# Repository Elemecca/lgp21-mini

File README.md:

# LGP-21 Mini

The LGP-21 is an early transistorized computer manufactured by
the Librascope division of General Precision starting in 1963.
If you want to see the original computer in action, Usagi Electric
created [a series of excellent videos][usagi].

This project is a miniature replica of the LGP-21. It aims to be
as close to electrically identical to the original as possible
without relying on out-of-production components like germanium
transistors.

[usagi]: https://www.youtube.com/playlist?list=PLnw98JPyObn17qO83Hy1PHKtXimH4rYbU

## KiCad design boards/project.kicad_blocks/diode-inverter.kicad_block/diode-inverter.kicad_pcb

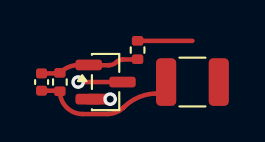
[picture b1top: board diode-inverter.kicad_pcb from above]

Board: 2 copper layers, 5 parts (0 on the bottom side), 2 nets.

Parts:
C17: 120p; C_0402_1005Metric
Q64: MMBT5401; SOT-23
R316: 6k8; R_0402_1005Metric
R355: 10k ½W; R_1210_3225Metric
R356: 33k; R_0402_1005Metric

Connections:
unnamed: C17.2, R316.1, R355.2
unnamed: C17.1, Q64.1 (B), R316.2, R356.1

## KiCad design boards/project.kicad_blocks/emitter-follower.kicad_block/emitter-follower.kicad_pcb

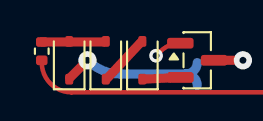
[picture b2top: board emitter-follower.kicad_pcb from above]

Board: 2 copper layers, 5 parts (0 on the bottom side), 3 nets.

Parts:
CR11, CR12, CR13: 1N4148WS; D_SOD-323
Q26: MMBT5401; SOT-23
R200: 56k; R_0402_1005Metric

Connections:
unnamed: CR12.1 (K), CR13.2 (A)
unnamed: CR13.1 (K), Q26.2 (E)
~G: CR11.2 (A), CR12.2 (A), R200.1

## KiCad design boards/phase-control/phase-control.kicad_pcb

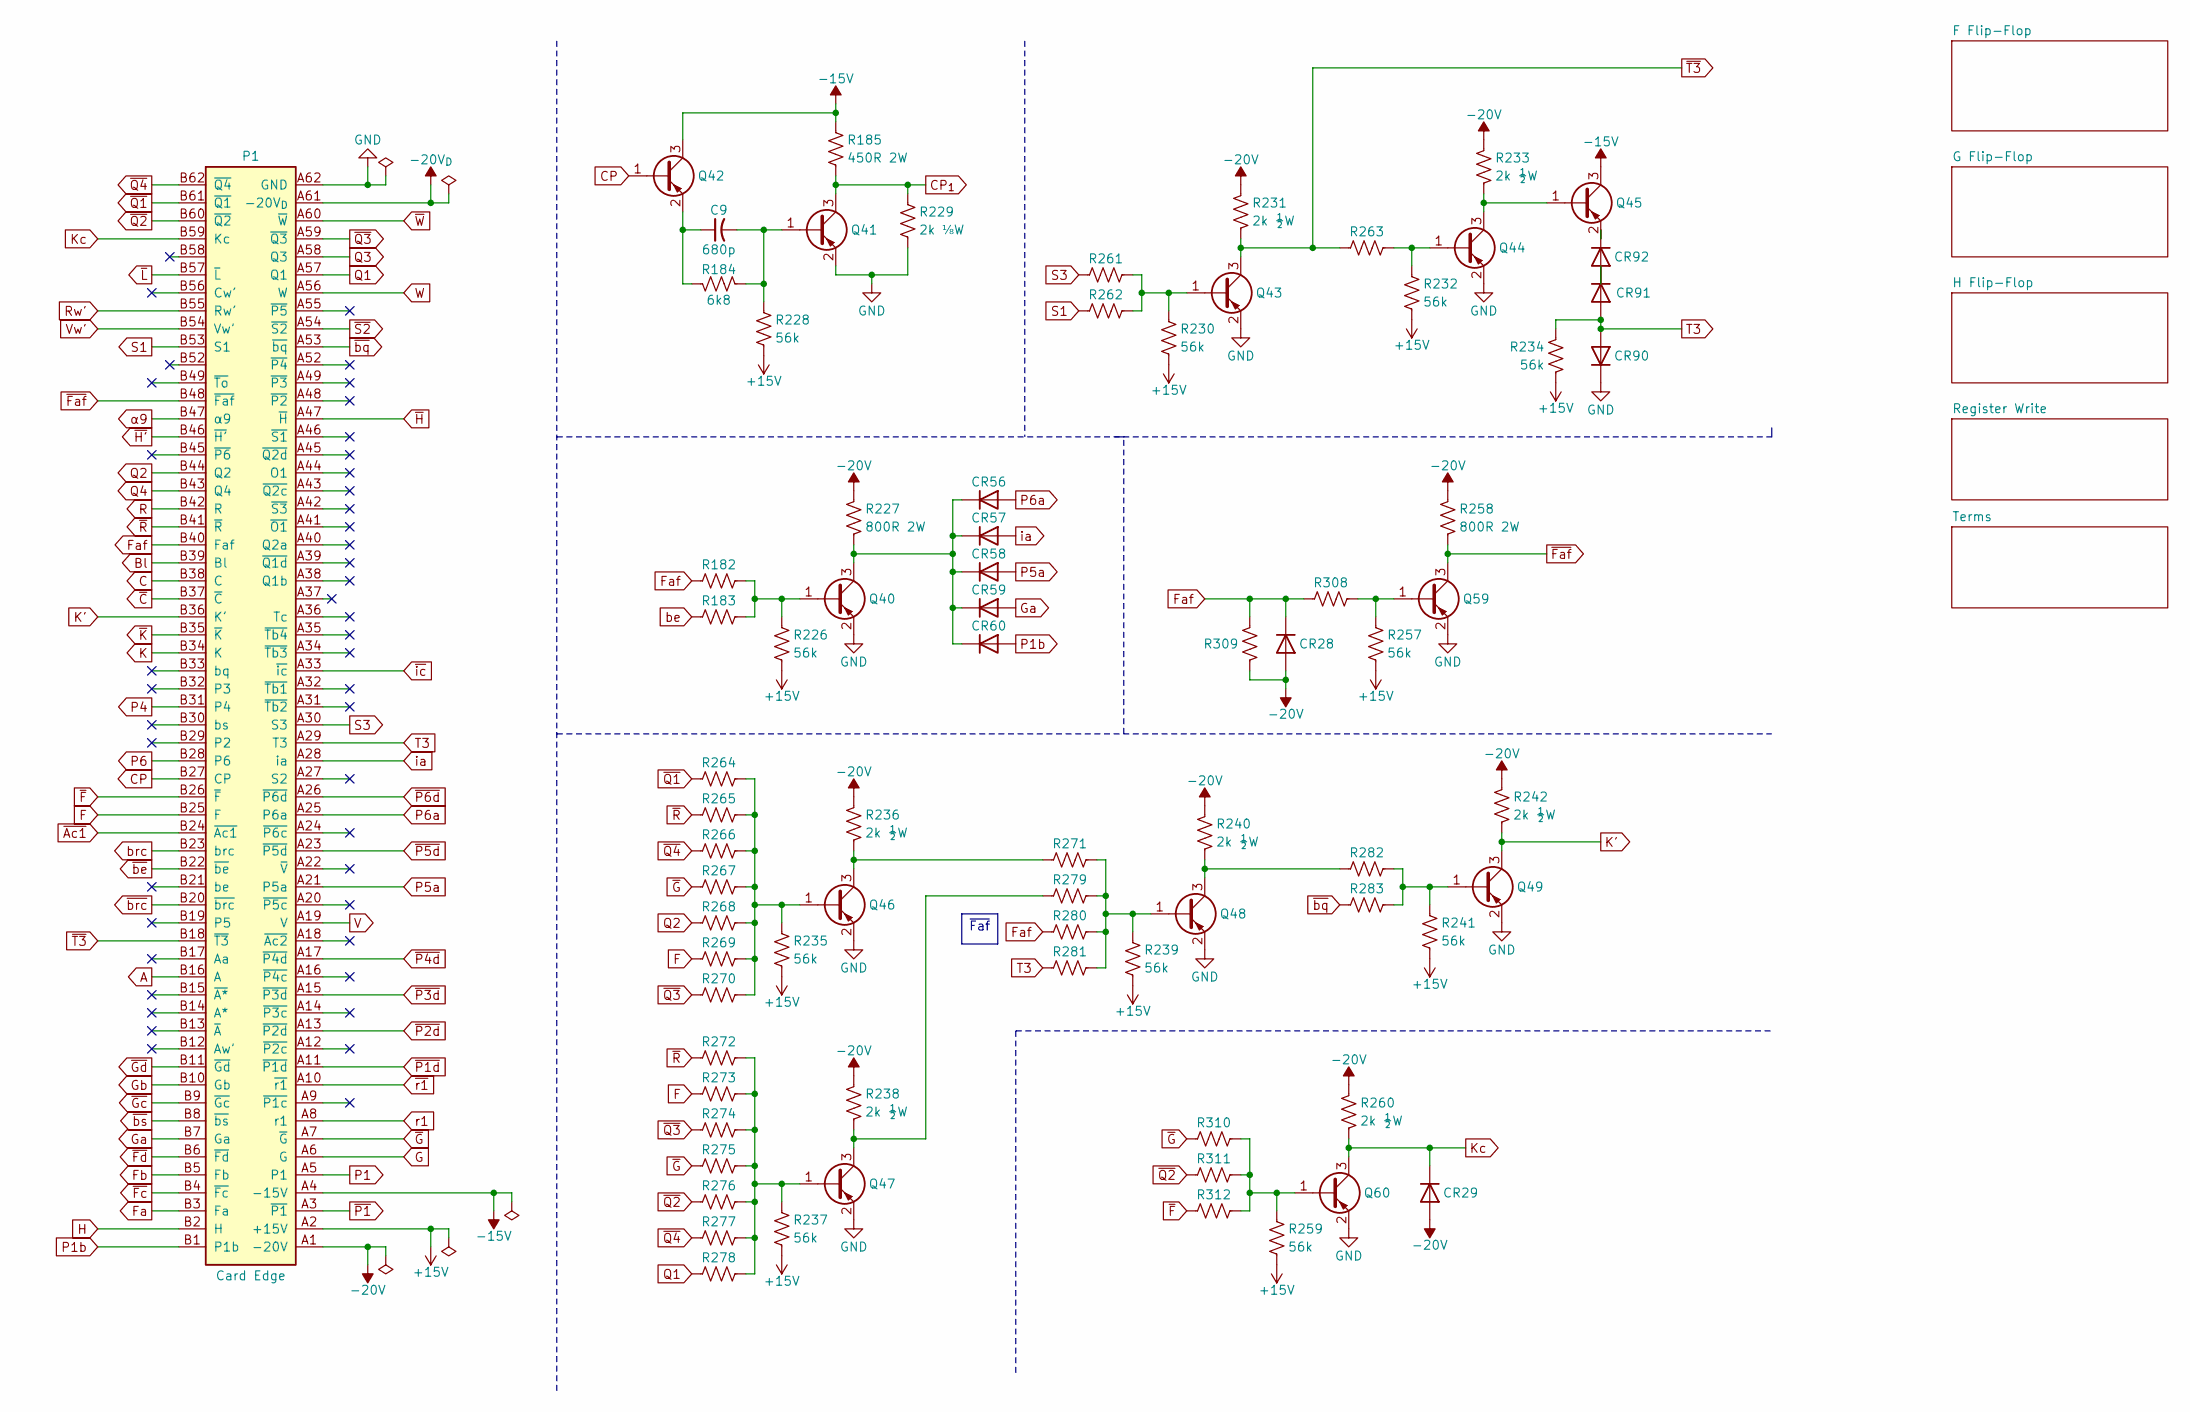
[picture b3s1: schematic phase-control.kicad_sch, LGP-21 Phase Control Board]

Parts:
C9: 680p; C_0402_1005Metric
CR28, CR29, CR56, CR57, CR58, CR59, CR60, CR90, CR91, CR92: 1N4148WS; D_SOD-323; LCSC C2128
P1: Card Edge; Bus_PCI_5V_32bit
Q40, Q41, Q42, Q43, Q44, Q45, Q46, Q47, Q48, Q49, Q59, Q60: MMBT5401; SOT-23; LCSC C8326
R182, R183, R261, R262, R263, R264, R265, R266, R267, R268, R269, R270, R271, R272, R273, R274, R275, R276, R277, R278, R279, R280, R281, R282, R283, R308, R309, R310, R311, R312: 15k; R_0402_1005Metric
R184: 6k8; R_0402_1005Metric
R185: 450R 2W; R_Axial_DIN0516_L15.5mm_D5.0mm_P20.32mm_Horizontal
R226, R228, R230, R232, R234, R235, R237, R239, R241, R257, R259: 56k; R_0402_1005Metric
R227, R258: 800R 2W; R_Axial_DIN0516_L15.5mm_D5.0mm_P20.32mm_Horizontal
R229: 2k ⅛W; R_0805_2012Metric
R231, R233, R236, R238, R240, R242, R260: 2k ½W; R_1210_3225Metric

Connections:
+15V: P1.A2 (+15V), R226.2, R228.2, R230.2, R232.2, R234.2, R235.2, R237.2, R239.2, R241.2, R257.2, R259.2; also elsewhere on the board
-15V: P1.A4 (-15V), Q42.3 (C), Q45.3 (C), R185.1; also elsewhere on the board
-20V: CR28.2 (A), CR29.2 (A), P1.A1 (-20V), R227.1, R231.1, R233.1, R236.1, R238.1, R240.1, R242.1, R258.1, R260.1, R309.2; also elsewhere on the board
-20V_{D}: P1.A61 (-20V_{D}); also elsewhere on the board
A: P1.B16 (A); also elsewhere on the board
Bl: P1.B39 (Bl); also elsewhere on the board
C: P1.B38 (C); also elsewhere on the board
CP: P1.B27 (CP), Q42.1 (B); also elsewhere on the board
CP_{1}: Q41.3 (C), R185.2, R229.1; also elsewhere on the board
F: P1.B25 (F), R269.1, R273.1; also elsewhere on the board
Fa: P1.B3 (Fa); also elsewhere on the board
Faf: CR28.1 (K), P1.B40 (Faf), R182.1, R280.1, R308.1, R309.1
Fb: P1.B5 (Fb); also elsewhere on the board
G: P1.A6 (G); also elsewhere on the board
GND: CR90.1 (K), P1.A62 (GND), Q40.2 (E), Q41.2 (E), Q43.2 (E), Q44.2 (E), Q46.2 (E), Q47.2 (E), Q48.2 (E), Q49.2 (E), Q59.2 (E), Q60.2 (E), R229.2; also elsewhere on the board
Ga: CR59.2 (A), P1.B7 (Ga); also elsewhere on the board
Gb: P1.B10 (Gb); also elsewhere on the board
H: P1.B2 (H); also elsewhere on the board
K: P1.B34 (K); also elsewhere on the board
K': P1.B36 (K'), Q49.3 (C), R242.2
Kc: CR29.1 (K), P1.B59 (Kc), Q60.3 (C), R260.2
unnamed: CR56.1 (K), CR57.1 (K), CR58.1 (K), CR59.1 (K), CR60.1 (K), Q40.3 (C), R227.2
unnamed: CR91.1 (K), CR92.2 (A)
unnamed: CR92.1 (K), Q45.2 (E)
unnamed: Q40.1 (B), R182.2, R183.2, R226.1
unnamed: C9.2, Q41.1 (B), R184.2, R228.1
unnamed: C9.1, Q42.2 (E), R184.1
unnamed: Q43.1 (B), R230.1, R261.2, R262.2
unnamed: Q44.1 (B), R232.1, R263.2
unnamed: Q44.3 (C), Q45.1 (B), R233.2
unnamed: Q46.1 (B), R235.1, R264.2, R265.2, R266.2, R267.2, R268.2, R269.2, R270.2
unnamed: Q46.3 (C), R236.2, R271.1
unnamed: Q47.1 (B), R237.1, R272.2, R273.2, R274.2, R275.2, R276.2, R277.2, R278.2
unnamed: Q47.3 (C), R238.2, R279.1
unnamed: Q48.1 (B), R239.1, R271.2, R279.2, R280.2, R281.2
unnamed: Q48.3 (C), R240.2, R282.1
unnamed: Q49.1 (B), R241.1, R282.2, R283.2
unnamed: Q59.1 (B), R257.1, R308.2
unnamed: Q60.1 (B), R259.1, R310.2, R311.2, R312.2
P1: P1.A5 (P1); also elsewhere on the board
P1b: CR60.2 (A), P1.B1 (P1b)
P4: P1.B31 (P4); also elsewhere on the board
P5a: CR58.2 (A), P1.A21 (P5a)
P6: P1.B28 (P6); also elsewhere on the board
P6a: CR56.2 (A), P1.A25 (P6a)
Q1: P1.A57 (Q1), R278.1; also elsewhere on the board
Q2: P1.B44 (Q2), R268.1; also elsewhere on the board
Q3: P1.A58 (Q3); also elsewhere on the board
Q4: P1.B43 (Q4); also elsewhere on the board
R: P1.B42 (R); also elsewhere on the board
Rw': P1.B55 (Rw'); also elsewhere on the board
S1: P1.B53 (S1), R262.1
S3: P1.A30 (S3), R261.1
T3: CR90.2 (A), CR91.2 (A), P1.A29 (T3), R234.1, R281.1; also elsewhere on the board
V: P1.A19 (V); also elsewhere on the board
Vw': P1.B54 (Vw'); also elsewhere on the board
W: P1.A56 (W); also elsewhere on the board
be: R183.1; also elsewhere on the board
brc: P1.B23 (brc); also elsewhere on the board
ia: CR57.2 (A), P1.A28 (ia)
r1: P1.A8 (r1); also elsewhere on the board
~Ac1: P1.B24 (~Ac1); also elsewhere on the board
~C: P1.B37 (~C); also elsewhere on the board
~Faf: P1.B48 (~Faf), Q59.3 (C), R258.2; also elsewhere on the board
~Fc: P1.B4 (~Fc); also elsewhere on the board
~Fd: P1.B6 (~Fd); also elsewhere on the board
~F: P1.B26 (~F), R312.1; also elsewhere on the board
~Gc: P1.B9 (~Gc); also elsewhere on the board
~Gd: P1.B11 (~Gd); also elsewhere on the board
~G: P1.A7 (~G), R267.1, R275.1, R310.1; also elsewhere on the board
~H': P1.B46 (~H'); also elsewhere on the board
~H: P1.A47 (~H); also elsewhere on the board
~K: P1.B35 (~K); also elsewhere on the board
~L: P1.B57 (~L); also elsewhere on the board
~P1d: P1.A11 (~P1d); also elsewhere on the board
~P1: P1.A3 (~P1); also elsewhere on the board
~P2d: P1.A13 (~P2d); also elsewhere on the board
~P3d: P1.A15 (~P3d); also elsewhere on the board
~P4d: P1.A17 (~P4d); also elsewhere on the board
~P5d: P1.A23 (~P5d); also elsewhere on the board
~P6d: P1.A26 (~P6d); also elsewhere on the board
~Q1: P1.B61 (~Q1), R264.1; also elsewhere on the board
~Q2: P1.B60 (~Q2), R276.1, R311.1; also elsewhere on the board
~Q3: P1.A59 (~Q3), R270.1, R274.1; also elsewhere on the board
~Q4: P1.B62 (~Q4), R266.1, R277.1; also elsewhere on the board
~R: P1.B41 (~R), R265.1, R272.1
~S2: P1.A54 (~S2); also elsewhere on the board
~T3: P1.B18 (~T3), Q43.3 (C), R231.2, R263.1
~W: P1.A60 (~W); also elsewhere on the board
~be: P1.B22 (~be); also elsewhere on the board
~bq: P1.A53 (~bq), R283.1
~brc: P1.B20 (~brc); also elsewhere on the board
~bs: P1.B8 (~bs); also elsewhere on the board
~ic: P1.A33 (~ic); also elsewhere on the board
~r1: P1.A10 (~r1); also elsewhere on the board
α9: P1.B47 (α9); also elsewhere on the board

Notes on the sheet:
~{Faf}

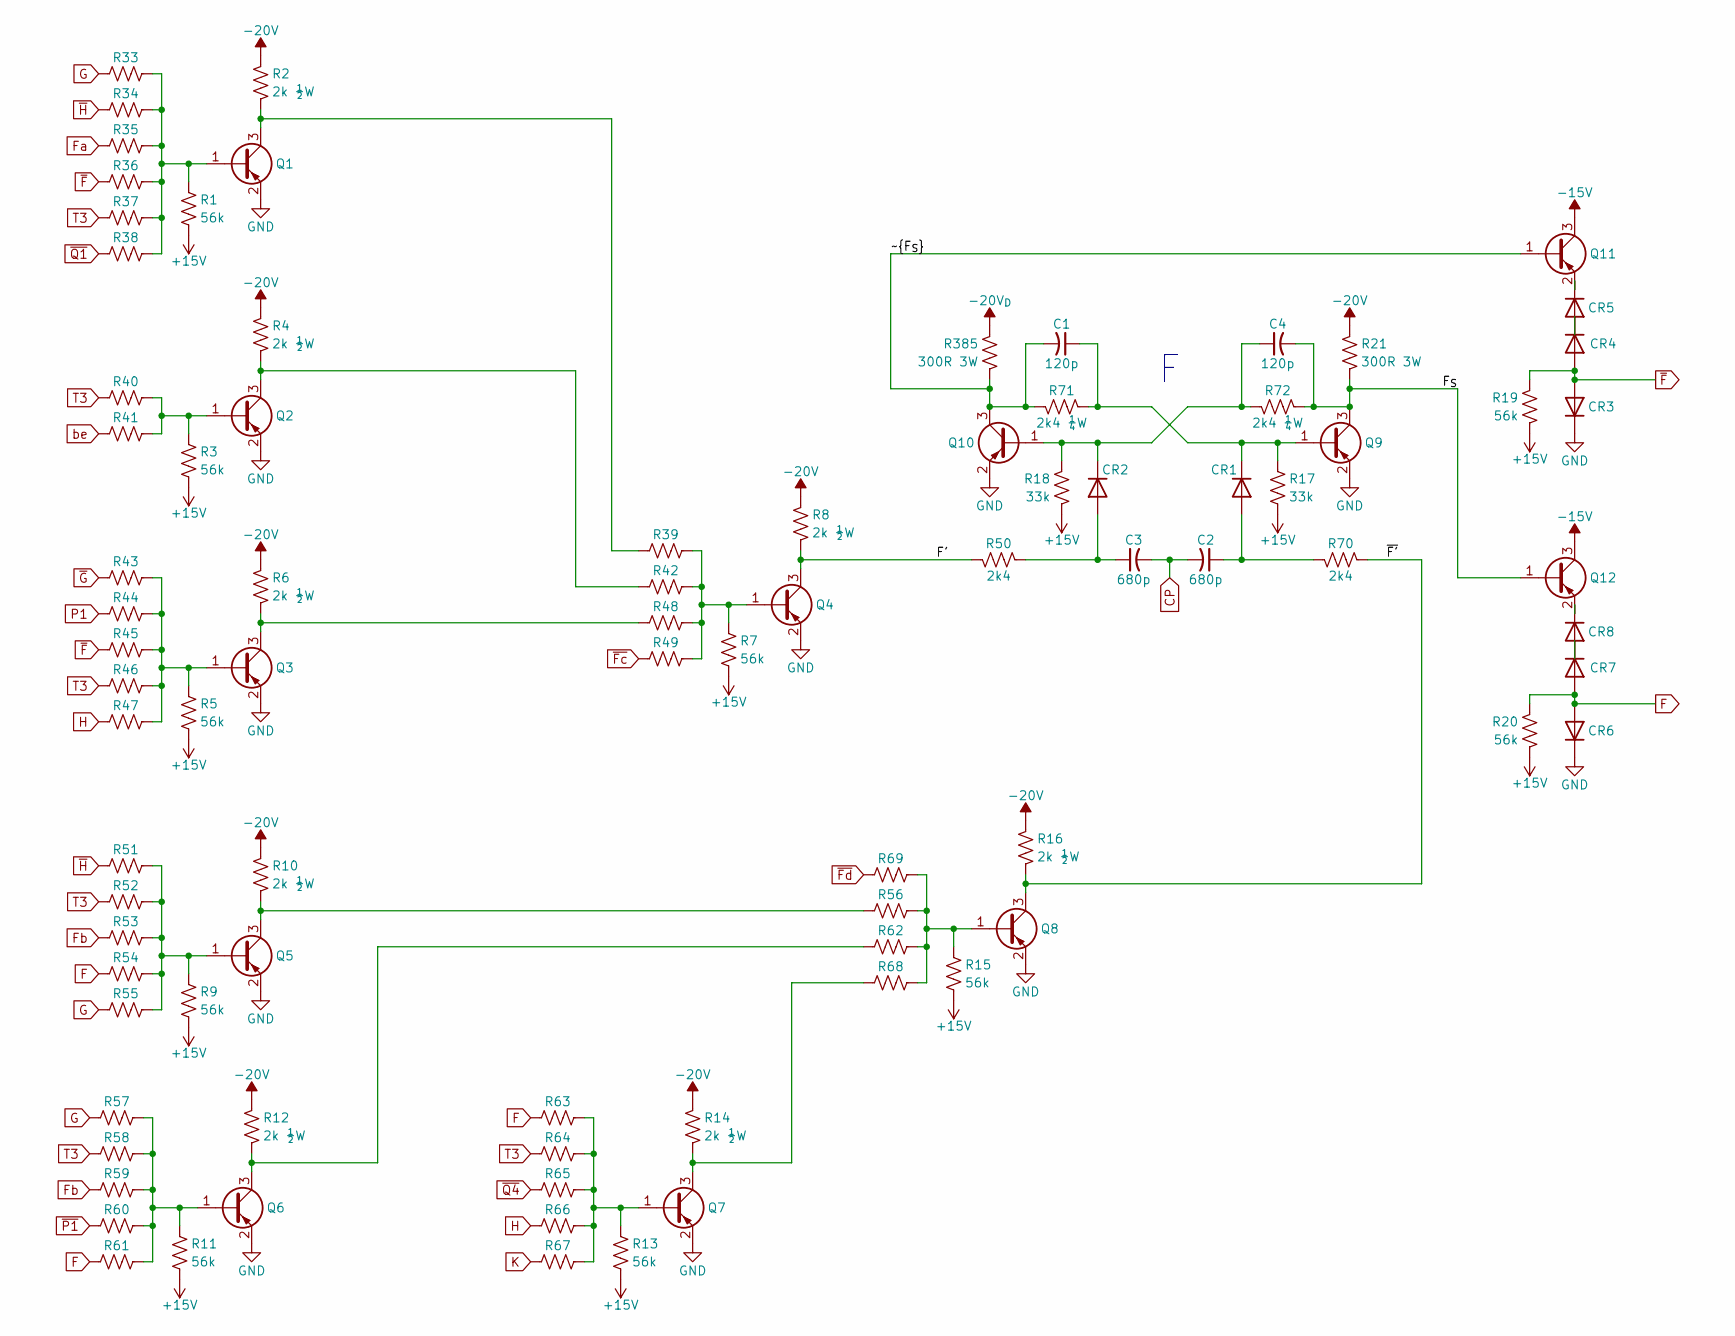
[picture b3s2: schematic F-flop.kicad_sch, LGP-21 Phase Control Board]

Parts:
C1, C4: 120p; C_0402_1005Metric
C2, C3: 680p; C_0402_1005Metric
CR1, CR2, CR3, CR4, CR5, CR6, CR7, CR8: 1N4148WS; D_SOD-323; LCSC C2128
Q1, Q2, Q3, Q4, Q5, Q6, Q7, Q8, Q9, Q10, Q11, Q12: MMBT5401; SOT-23; LCSC C8326
R1, R3, R5, R7, R9, R11, R13, R15, R19, R20: 56k; R_0402_1005Metric
R2, R4, R6, R8, R10, R12, R14, R16: 2k ½W; R_1210_3225Metric
R17, R18: 33k; R_0402_1005Metric
R21, R385: 300R 3W; R_Axial_DIN0516_L15.5mm_D5.0mm_P20.32mm_Horizontal
R33, R34, R35, R36, R37, R38, R39, R40, R41, R42, R43, R44, R45, R46, R47, R48, R49, R51, R52, R53, R54, R55, R56, R57, R58, R59, R60, R61, R62, R63, R64, R65, R66, R67, R68, R69: 15k; R_0402_1005Metric
R50, R70: 2k4; R_0402_1005Metric
R71, R72: 2k4 ¼W; R_0603_1608Metric

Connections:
+15V: R1.2, R3.2, R5.2, R7.2, R9.2, R11.2, R13.2, R15.2, R17.2, R18.2, R19.2, R20.2; also elsewhere on the board
-15V: Q11.3 (C), Q12.3 (C); also elsewhere on the board
-20V: R2.1, R4.1, R6.1, R8.1, R10.1, R12.1, R14.1, R16.1, R21.1; also elsewhere on the board
-20V_{D}: R385.1; also elsewhere on the board
/F Flip-Flop/F': Q4.3 (C), R8.2, R50.1
/F Flip-Flop/F_{S}: C4.2, Q9.3 (C), Q12.1 (B), R21.2, R72.2
/F Flip-Flop/~F': Q8.3 (C), R16.2, R70.2
/F Flip-Flop/~F_{S}: C1.2, Q10.3 (C), Q11.1 (B), R71.1, R385.2
CP: C2.2, C3.2; also elsewhere on the board
F: CR6.2 (A), CR7.2 (A), R20.1, R54.1, R61.1, R63.1; also elsewhere on the board
Fa: R35.1; also elsewhere on the board
Fb: R53.1, R59.1; also elsewhere on the board
G: R33.1, R55.1, R57.1; also elsewhere on the board
GND: CR3.1 (K), CR6.1 (K), Q1.2 (E), Q2.2 (E), Q3.2 (E), Q4.2 (E), Q5.2 (E), Q6.2 (E), Q7.2 (E), Q8.2 (E), Q9.2 (E), Q10.2 (E); also elsewhere on the board
H: R47.1, R66.1; also elsewhere on the board
K: R67.1; also elsewhere on the board
unnamed: C2.1, CR1.2 (A), R70.1
unnamed: C1.1, CR1.1 (K), Q9.1 (B), R17.1, R71.2
unnamed: C3.1, CR2.2 (A), R50.2
unnamed: C4.1, CR2.1 (K), Q10.1 (B), R18.1, R72.1
unnamed: CR4.1 (K), CR5.2 (A)
unnamed: CR5.1 (K), Q11.2 (E)
unnamed: CR7.1 (K), CR8.2 (A)
unnamed: CR8.1 (K), Q12.2 (E)
unnamed: Q1.1 (B), R1.1, R33.2, R34.2, R35.2, R36.2, R37.2, R38.2
unnamed: Q1.3 (C), R2.2, R39.1
unnamed: Q2.1 (B), R3.1, R40.2, R41.2
unnamed: Q2.3 (C), R4.2, R42.1
unnamed: Q3.1 (B), R5.1, R43.2, R44.2, R45.2, R46.2, R47.2
unnamed: Q3.3 (C), R6.2, R48.1
unnamed: Q4.1 (B), R7.1, R39.2, R42.2, R48.2, R49.2
unnamed: Q5.1 (B), R9.1, R51.2, R52.2, R53.2, R54.2, R55.2
unnamed: Q5.3 (C), R10.2, R56.1
unnamed: Q6.1 (B), R11.1, R57.2, R58.2, R59.2, R60.2, R61.2
unnamed: Q6.3 (C), R12.2, R62.1
unnamed: Q7.1 (B), R13.1, R63.2, R64.2, R65.2, R66.2, R67.2
unnamed: Q7.3 (C), R14.2, R68.1
unnamed: Q8.1 (B), R15.1, R56.2, R62.2, R68.2, R69.2
P1: R44.1; also elsewhere on the board
T3: R37.1, R40.1, R46.1, R52.1, R58.1, R64.1; also elsewhere on the board
be: R41.1; also elsewhere on the board
~Fc: R49.1; also elsewhere on the board
~Fd: R69.1; also elsewhere on the board
~F: CR3.2 (A), CR4.2 (A), R19.1, R36.1, R45.1; also elsewhere on the board
~G: R43.1; also elsewhere on the board
~H: R34.1, R51.1; also elsewhere on the board
~P1: R60.1; also elsewhere on the board
~Q1: R38.1; also elsewhere on the board
~Q4: R65.1; also elsewhere on the board

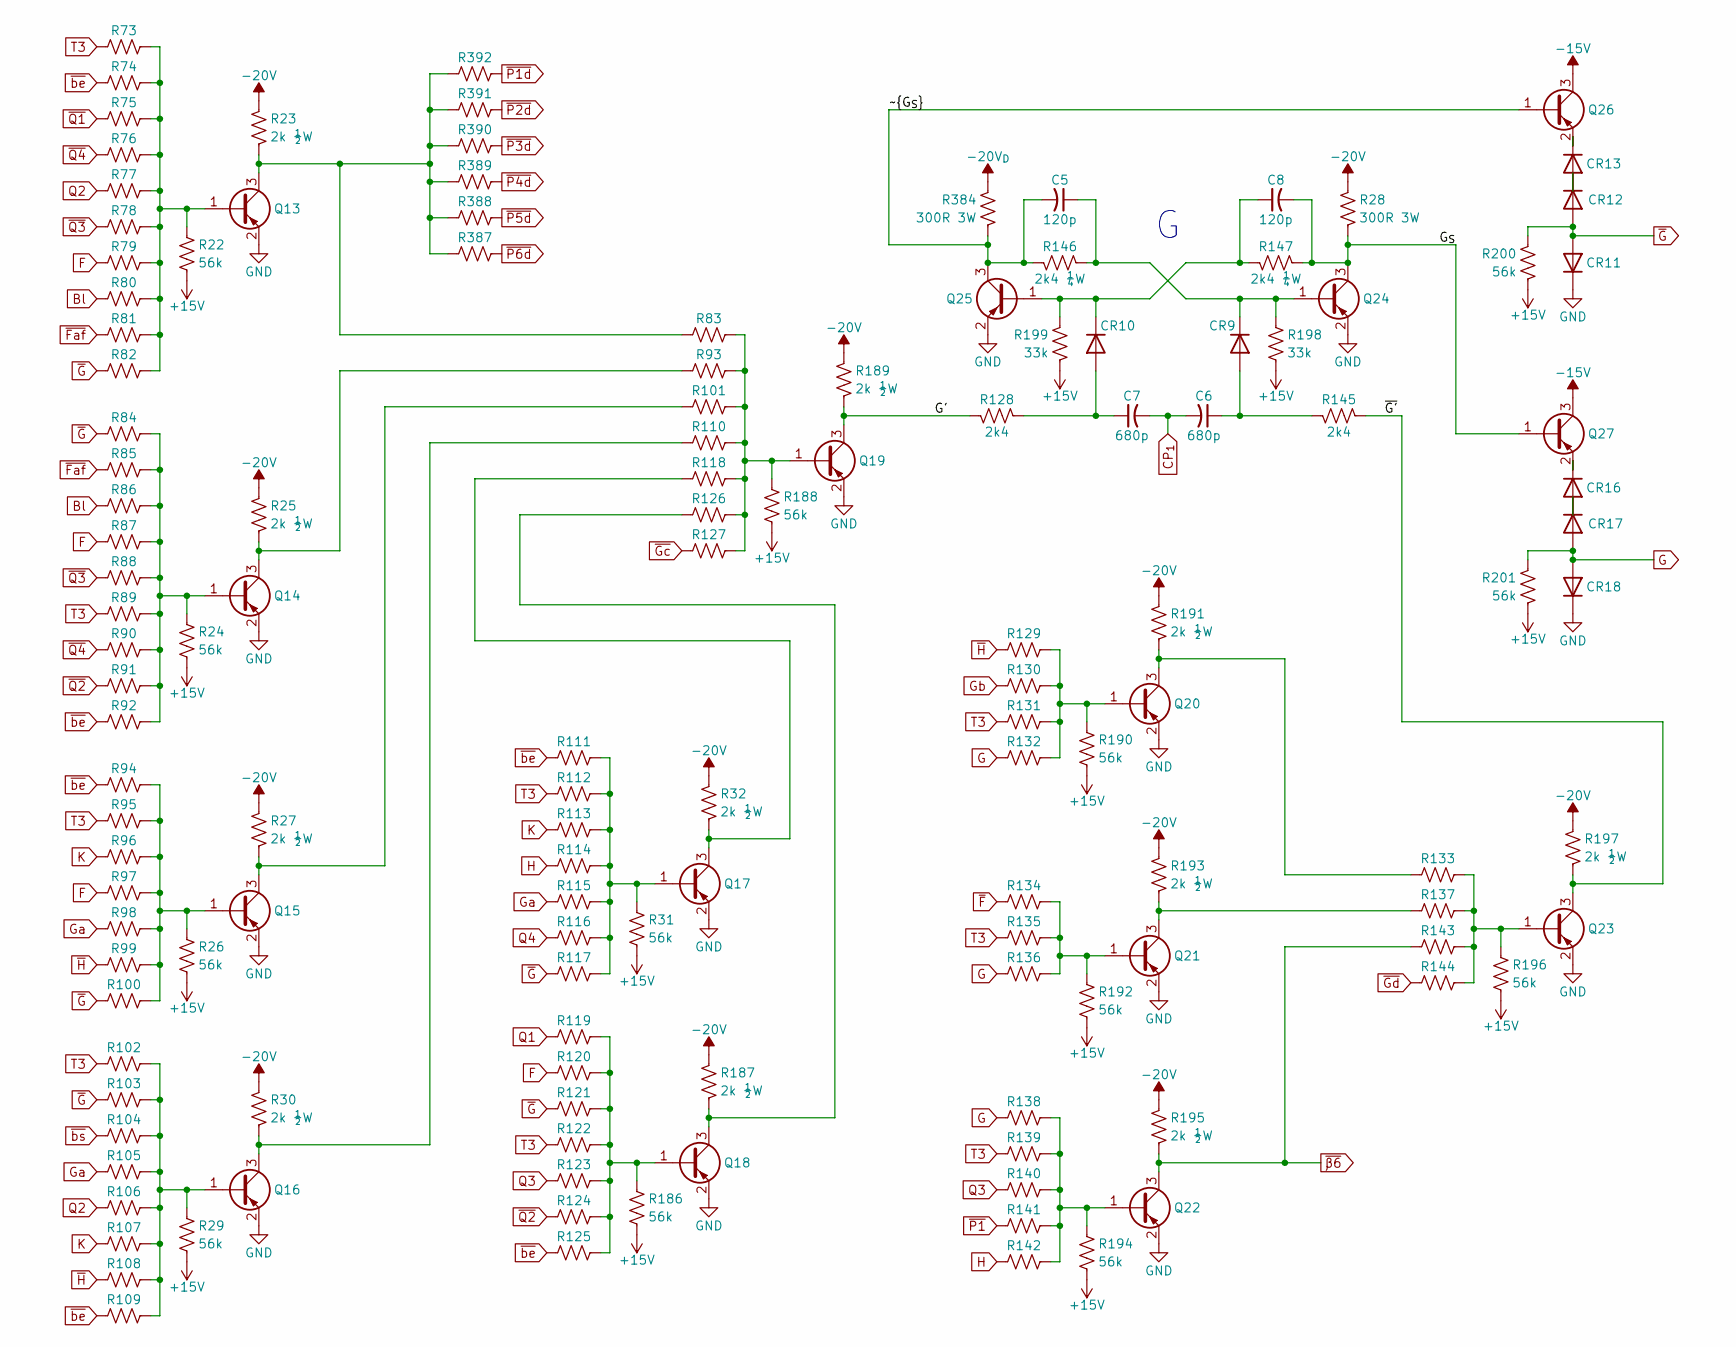
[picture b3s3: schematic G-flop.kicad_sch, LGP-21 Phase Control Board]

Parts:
C5, C8: 120p; C_0402_1005Metric
C6, C7: 680p; C_0402_1005Metric
CR9, CR10, CR11, CR12, CR13, CR16, CR17, CR18: 1N4148WS; D_SOD-323; LCSC C2128
Q13, Q14, Q15, Q16, Q17, Q18, Q19, Q20, Q21, Q22, Q23, Q24, Q25, Q26, Q27: MMBT5401; SOT-23; LCSC C8326
R22, R24, R26, R29, R31, R186, R188, R190, R192, R194, R196, R200, R201: 56k; R_0402_1005Metric
R23, R25, R27, R30, R32, R187, R189, R191, R193, R195, R197: 2k ½W; R_1210_3225Metric
R28, R384: 300R 3W; R_Axial_DIN0516_L15.5mm_D5.0mm_P20.32mm_Horizontal
R73, R74, R75, R76, R77, R78, R79, R80, R81, R82, R83, R84, R85, R86, R87, R88, R89, R90, R91, R92, R93, R94, R95, R96, R97, R98, R99, R100, R101, R102, R103, R104, R105, R106, R107, R108, R109, R110, R111, R112, R113, R114, R115, R116, R117, R118, R119, R120, R121, R122, R123, R124, R125, R126, R127, R129, R130, R131, R132, R133, R134, R135, R136, R137, R138, R139, R140, R141, R142, R143, R144, R387, R388, R389, R390, R391, R392: 15k; R_0402_1005Metric
R128, R145: 2k4; R_0402_1005Metric
R146, R147: 2k4 ¼W; R_0603_1608Metric
R198, R199: 33k; R_0402_1005Metric

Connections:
+15V: R22.2, R24.2, R26.2, R29.2, R31.2, R186.2, R188.2, R190.2, R192.2, R194.2, R196.2, R198.2, R199.2, R200.2, R201.2; also elsewhere on the board
-15V: Q26.3 (C), Q27.3 (C); also elsewhere on the board
-20V: R23.1, R25.1, R27.1, R28.1, R30.1, R32.1, R187.1, R189.1, R191.1, R193.1, R195.1, R197.1; also elsewhere on the board
-20V_{D}: R384.1; also elsewhere on the board
/G Flip-Flop/G': Q19.3 (C), R128.1, R189.2
/G Flip-Flop/G_{S}: C8.2, Q24.3 (C), Q27.1 (B), R28.2, R147.2
/G Flip-Flop/~G': Q23.3 (C), R145.2, R197.2
/G Flip-Flop/~G_{S}: C5.2, Q25.3 (C), Q26.1 (B), R146.1, R384.2
Bl: R80.1, R86.1; also elsewhere on the board
CP_{1}: C6.2, C7.2; also elsewhere on the board
F: R79.1, R87.1, R97.1, R120.1; also elsewhere on the board
G: CR17.2 (A), CR18.2 (A), R132.1, R136.1, R138.1, R201.1; also elsewhere on the board
GND: CR11.1 (K), CR18.1 (K), Q13.2 (E), Q14.2 (E), Q15.2 (E), Q16.2 (E), Q17.2 (E), Q18.2 (E), Q19.2 (E), Q20.2 (E), Q21.2 (E), Q22.2 (E), Q23.2 (E), Q24.2 (E), Q25.2 (E); also elsewhere on the board
Ga: R98.1, R105.1, R115.1; also elsewhere on the board
Gb: R130.1; also elsewhere on the board
H: R114.1, R142.1; also elsewhere on the board
K: R96.1, R107.1, R113.1; also elsewhere on the board
unnamed: C6.1, CR9.2 (A), R145.1
unnamed: C5.1, CR9.1 (K), Q24.1 (B), R146.2, R198.1
unnamed: C7.1, CR10.2 (A), R128.2
unnamed: C8.1, CR10.1 (K), Q25.1 (B), R147.1, R199.1
unnamed: CR12.1 (K), CR13.2 (A)
unnamed: CR13.1 (K), Q26.2 (E)
unnamed: CR16.2 (A), CR17.1 (K)
unnamed: CR16.1 (K), Q27.2 (E)
unnamed: Q13.1 (B), R22.1, R73.2, R74.2, R75.2, R76.2, R77.2, R78.2, R79.2, R80.2, R81.2, R82.2
unnamed: Q13.3 (C), R23.2, R83.1, R387.1, R388.1, R389.1, R390.1, R391.1, R392.1
unnamed: Q14.1 (B), R24.1, R84.2, R85.2, R86.2, R87.2, R88.2, R89.2, R90.2, R91.2, R92.2
unnamed: Q14.3 (C), R25.2, R93.1
unnamed: Q15.1 (B), R26.1, R94.2, R95.2, R96.2, R97.2, R98.2, R99.2, R100.2
unnamed: Q15.3 (C), R27.2, R101.1
unnamed: Q16.1 (B), R29.1, R102.2, R103.2, R104.2, R105.2, R106.2, R107.2, R108.2, R109.2
unnamed: Q16.3 (C), R30.2, R110.1
unnamed: Q17.1 (B), R31.1, R111.2, R112.2, R113.2, R114.2, R115.2, R116.2, R117.2
unnamed: Q17.3 (C), R32.2, R118.1
unnamed: Q18.1 (B), R119.2, R120.2, R121.2, R122.2, R123.2, R124.2, R125.2, R186.1
unnamed: Q18.3 (C), R126.1, R187.2
unnamed: Q19.1 (B), R83.2, R93.2, R101.2, R110.2, R118.2, R126.2, R127.2, R188.1
unnamed: Q20.1 (B), R129.2, R130.2, R131.2, R132.2, R190.1
unnamed: Q20.3 (C), R133.1, R191.2
unnamed: Q21.1 (B), R134.2, R135.2, R136.2, R192.1
unnamed: Q21.3 (C), R137.1, R193.2
unnamed: Q22.1 (B), R138.2, R139.2, R140.2, R141.2, R142.2, R194.1
unnamed: Q23.1 (B), R133.2, R137.2, R143.2, R144.2, R196.1
Q1: R119.1; also elsewhere on the board
Q2: R77.1, R106.1; also elsewhere on the board
Q3: R123.1, R140.1; also elsewhere on the board
Q4: R116.1; also elsewhere on the board
T3: R73.1, R89.1, R95.1, R102.1, R112.1, R122.1, R131.1, R135.1, R139.1; also elsewhere on the board
~Faf: R81.1, R85.1; also elsewhere on the board
~F: R134.1; also elsewhere on the board
~Gc: R127.1; also elsewhere on the board
~Gd: R144.1; also elsewhere on the board
~G: CR11.2 (A), CR12.2 (A), R82.1, R84.1, R100.1, R103.1, R117.1, R121.1, R200.1; also elsewhere on the board
~H: R99.1, R108.1, R129.1; also elsewhere on the board
~P1d: R392.2; also elsewhere on the board
~P1: R141.1; also elsewhere on the board
~P2d: R391.2; also elsewhere on the board
~P3d: R390.2; also elsewhere on the board
~P4d: R389.2; also elsewhere on the board
~P5d: R388.2; also elsewhere on the board
~P6d: R387.2; also elsewhere on the board
~Q1: R75.1; also elsewhere on the board
~Q2: R91.1, R124.1; also elsewhere on the board
~Q3: R78.1, R88.1; also elsewhere on the board
~Q4: R76.1, R90.1; also elsewhere on the board
~be: R74.1, R92.1, R94.1, R109.1, R111.1, R125.1; also elsewhere on the board
~bs: R104.1; also elsewhere on the board
~β6: Q22.3 (C), R143.1, R195.2; also elsewhere on the board

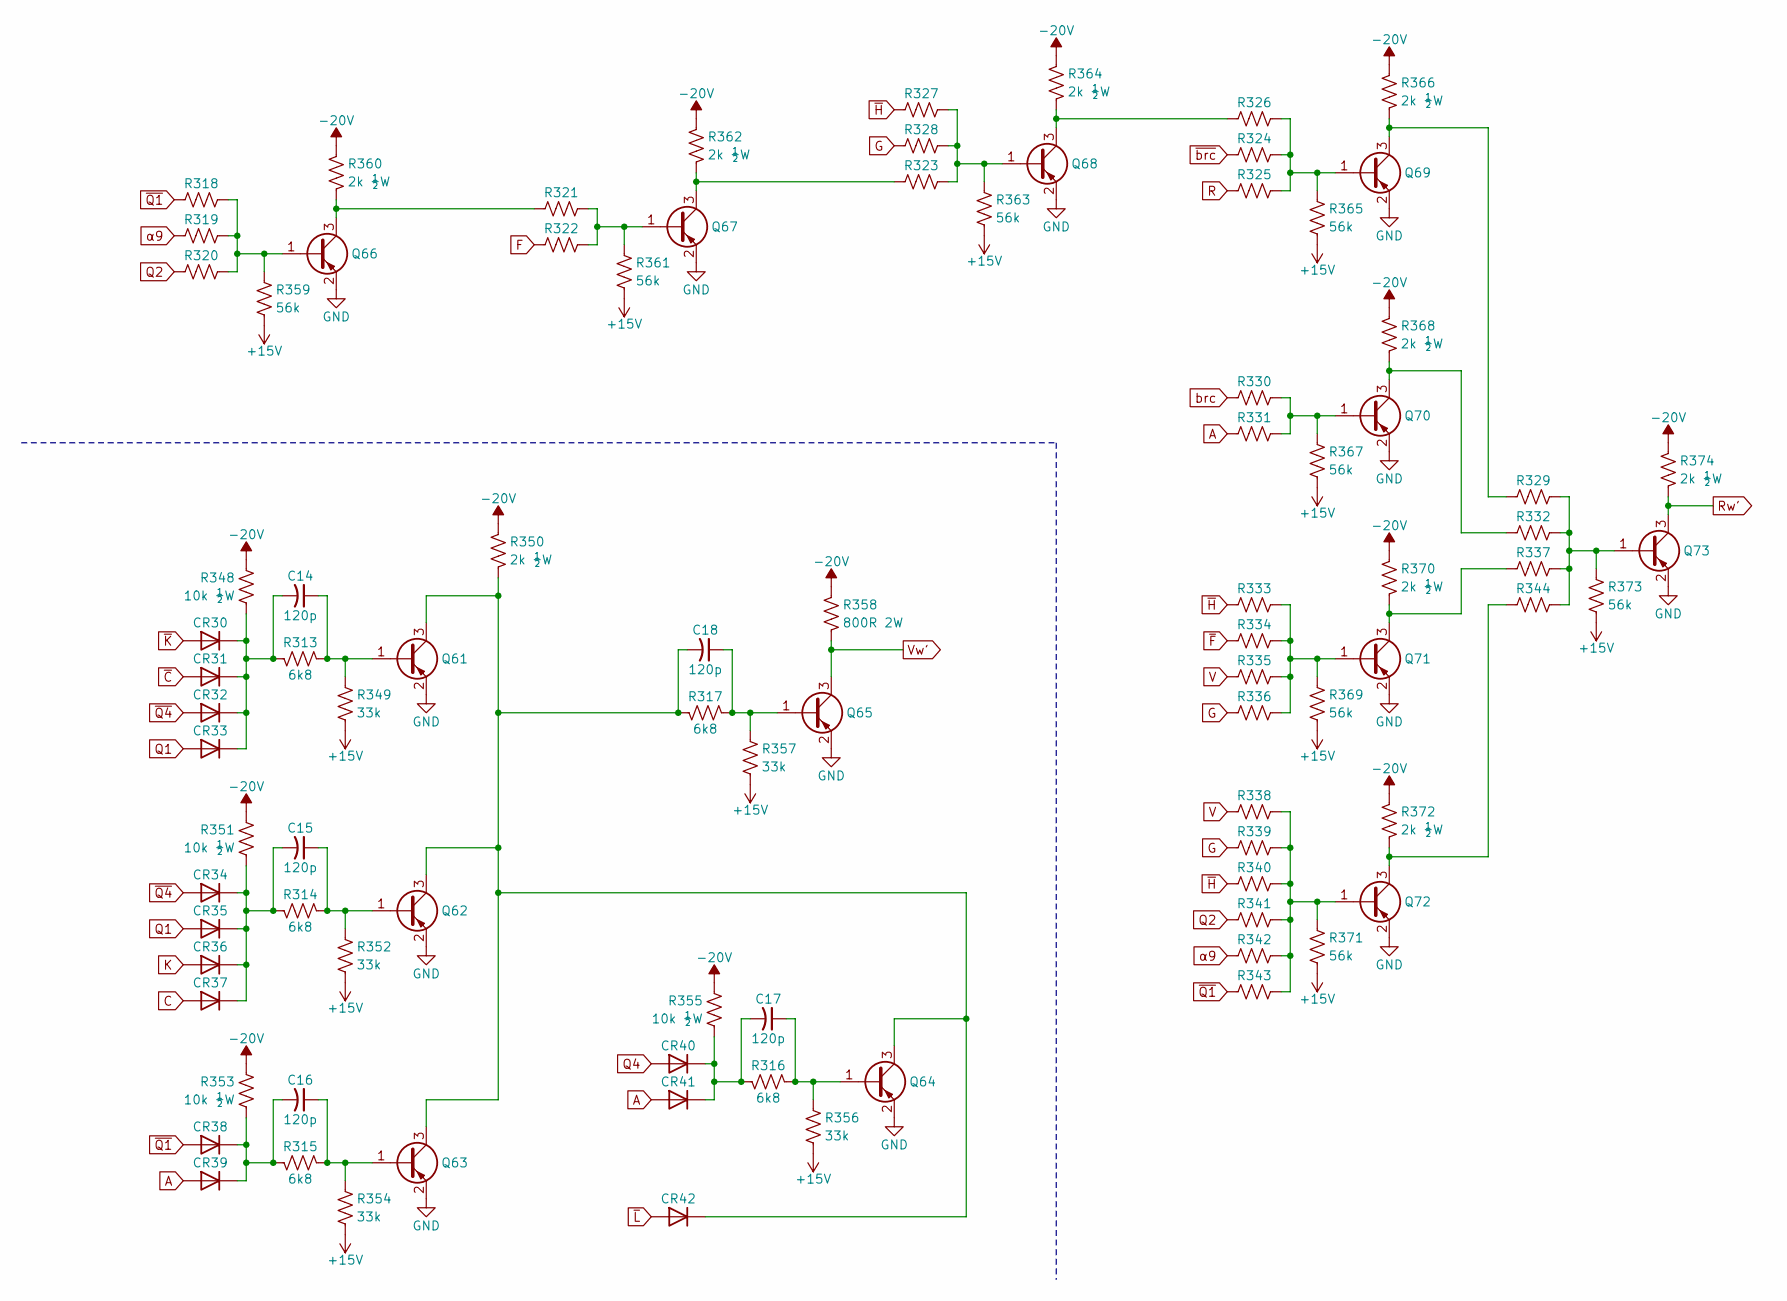
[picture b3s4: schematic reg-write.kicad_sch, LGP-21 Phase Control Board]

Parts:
C14, C15, C16, C17, C18: 120p; C_0402_1005Metric
CR30, CR31, CR32, CR33, CR34, CR35, CR36, CR37, CR38, CR39, CR40, CR41, CR42: 1N4148WS; D_SOD-323; LCSC C2128
Q61, Q62, Q63, Q64, Q65, Q66, Q67, Q68, Q69, Q70, Q71, Q72, Q73: MMBT5401; SOT-23; LCSC C8326
R313, R314, R315, R316, R317: 6k8; R_0402_1005Metric
R318, R319, R320, R321, R322, R323, R324, R325, R326, R327, R328, R329, R330, R331, R332, R333, R334, R335, R336, R337, R338, R339, R340, R341, R342, R343, R344: 15k; R_0402_1005Metric
R348, R351, R353, R355: 10k ½W; R_1210_3225Metric
R349, R352, R354, R356, R357: 33k; R_0402_1005Metric
R350, R360, R362, R364, R366, R368, R370, R372, R374: 2k ½W; R_1210_3225Metric
R358: 800R 2W; R_Axial_DIN0516_L15.5mm_D5.0mm_P20.32mm_Horizontal
R359, R361, R363, R365, R367, R369, R371, R373: 56k; R_0402_1005Metric

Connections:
+15V: R349.2, R352.2, R354.2, R356.2, R357.2, R359.2, R361.2, R363.2, R365.2, R367.2, R369.2, R371.2, R373.2; also elsewhere on the board
-20V: R348.1, R350.1, R351.1, R353.1, R355.1, R358.1, R360.1, R362.1, R364.1, R366.1, R368.1, R370.1, R372.1, R374.1; also elsewhere on the board
A: CR39.2 (A), CR41.2 (A), R331.1; also elsewhere on the board
C: CR37.2 (A); also elsewhere on the board
F: R322.1; also elsewhere on the board
G: R328.1, R336.1, R339.1; also elsewhere on the board
GND: Q61.2 (E), Q62.2 (E), Q63.2 (E), Q64.2 (E), Q65.2 (E), Q66.2 (E), Q67.2 (E), Q68.2 (E), Q69.2 (E), Q70.2 (E), Q71.2 (E), Q72.2 (E), Q73.2 (E); also elsewhere on the board
K: CR36.2 (A); also elsewhere on the board
unnamed: C14.2, CR30.1 (K), CR31.1 (K), CR32.1 (K), CR33.1 (K), R313.1, R348.2
unnamed: C15.2, CR34.1 (K), CR35.1 (K), CR36.1 (K), CR37.1 (K), R314.1, R351.2
unnamed: C16.2, CR38.1 (K), CR39.1 (K), R315.1, R353.2
unnamed: C17.2, CR40.1 (K), CR41.1 (K), R316.1, R355.2
unnamed: C18.2, CR42.1 (K), Q61.3 (C), Q62.3 (C), Q63.3 (C), Q64.3 (C), R317.1, R350.2
unnamed: C14.1, Q61.1 (B), R313.2, R349.1
unnamed: C15.1, Q62.1 (B), R314.2, R352.1
unnamed: C16.1, Q63.1 (B), R315.2, R354.1
unnamed: C17.1, Q64.1 (B), R316.2, R356.1
unnamed: C18.1, Q65.1 (B), R317.2, R357.1
unnamed: Q66.1 (B), R318.2, R319.2, R320.2, R359.1
unnamed: Q66.3 (C), R321.1, R360.2
unnamed: Q67.1 (B), R321.2, R322.2, R361.1
unnamed: Q67.3 (C), R323.1, R362.2
unnamed: Q68.1 (B), R323.2, R327.2, R328.2, R363.1
unnamed: Q68.3 (C), R326.1, R364.2
unnamed: Q69.1 (B), R324.2, R325.2, R326.2, R365.1
unnamed: Q69.3 (C), R329.1, R366.2
unnamed: Q70.1 (B), R330.2, R331.2, R367.1
unnamed: Q70.3 (C), R332.1, R368.2
unnamed: Q71.1 (B), R333.2, R334.2, R335.2, R336.2, R369.1
unnamed: Q71.3 (C), R337.1, R370.2
unnamed: Q72.1 (B), R338.2, R339.2, R340.2, R341.2, R342.2, R343.2, R371.1
unnamed: Q72.3 (C), R344.1, R372.2
unnamed: Q73.1 (B), R329.2, R332.2, R337.2, R344.2, R373.1
Q1: CR33.2 (A), CR35.2 (A); also elsewhere on the board
Q2: R320.1, R341.1; also elsewhere on the board
Q4: CR40.2 (A); also elsewhere on the board
R: R325.1; also elsewhere on the board
Rw': Q73.3 (C), R374.2; also elsewhere on the board
V: R335.1, R338.1; also elsewhere on the board
Vw': Q65.3 (C), R358.2; also elsewhere on the board
brc: R330.1; also elsewhere on the board
~C: CR31.2 (A); also elsewhere on the board
~F: R334.1; also elsewhere on the board
~H: R327.1, R333.1, R340.1; also elsewhere on the board
~K: CR30.2 (A); also elsewhere on the board
~L: CR42.2 (A); also elsewhere on the board
~Q1: CR38.2 (A), R318.1, R343.1; also elsewhere on the board
~Q4: CR32.2 (A), CR34.2 (A); also elsewhere on the board
~brc: R324.1; also elsewhere on the board
α9: R319.1, R342.1; also elsewhere on the board

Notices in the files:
boards/phase-control/F-flop.kicad_sch:
© 1962 General Precision; redrawn by Sam Hanes
boards/phase-control/phase-control.kicad_pcb:
© 2026 Sam Hanes, licensed CERN-OHL-W v2
